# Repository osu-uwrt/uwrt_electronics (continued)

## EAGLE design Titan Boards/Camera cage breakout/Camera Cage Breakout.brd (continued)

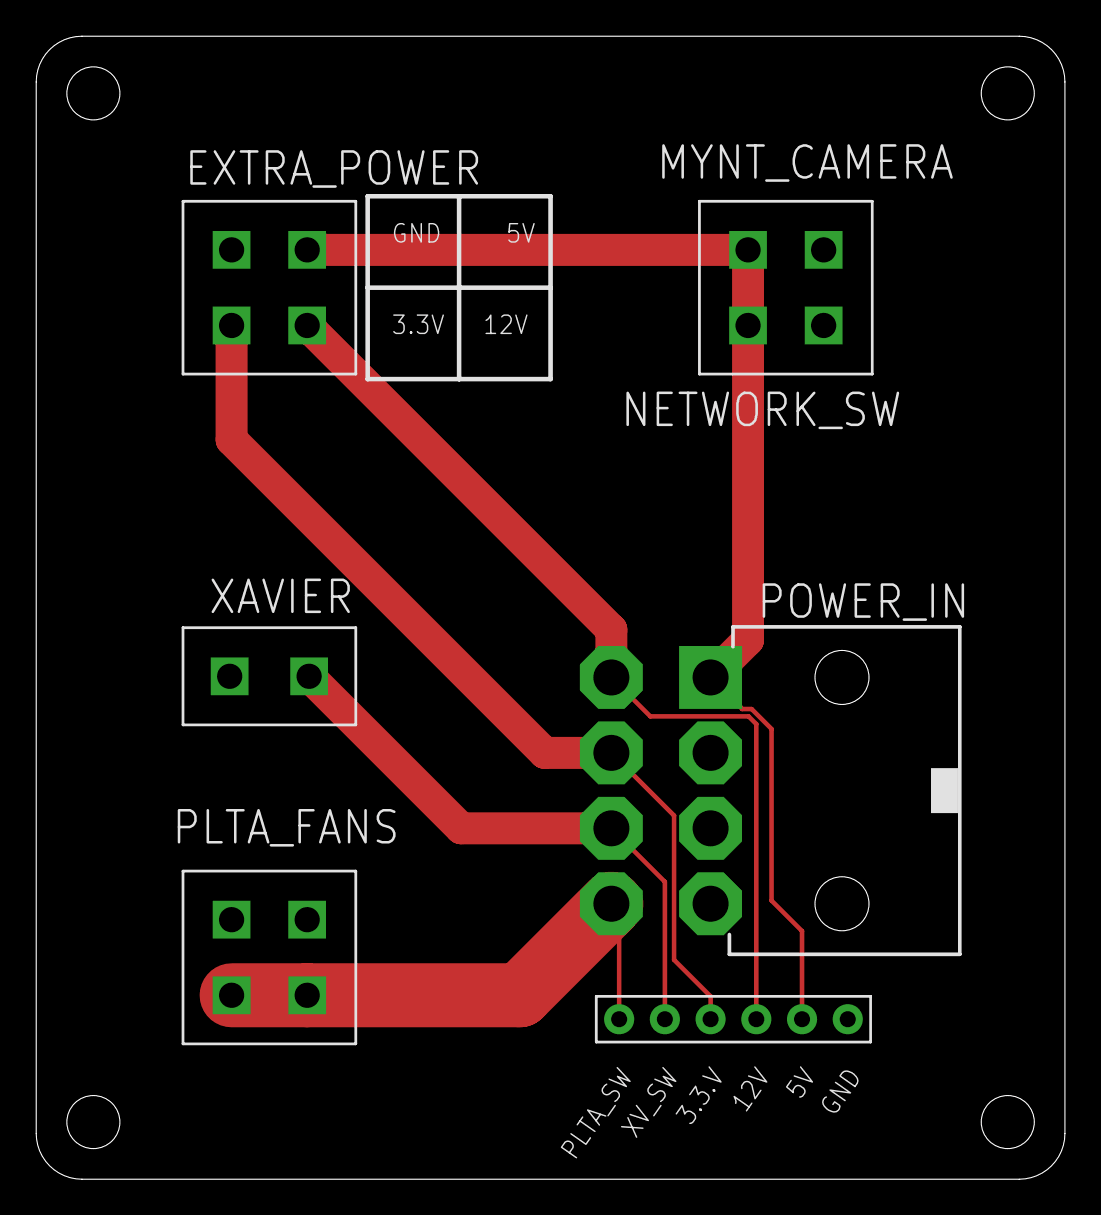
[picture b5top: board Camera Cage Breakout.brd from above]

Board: 2 copper layers, 57.1 x 63.5 mm, 6 parts (0 on the bottom side), 6 nets.

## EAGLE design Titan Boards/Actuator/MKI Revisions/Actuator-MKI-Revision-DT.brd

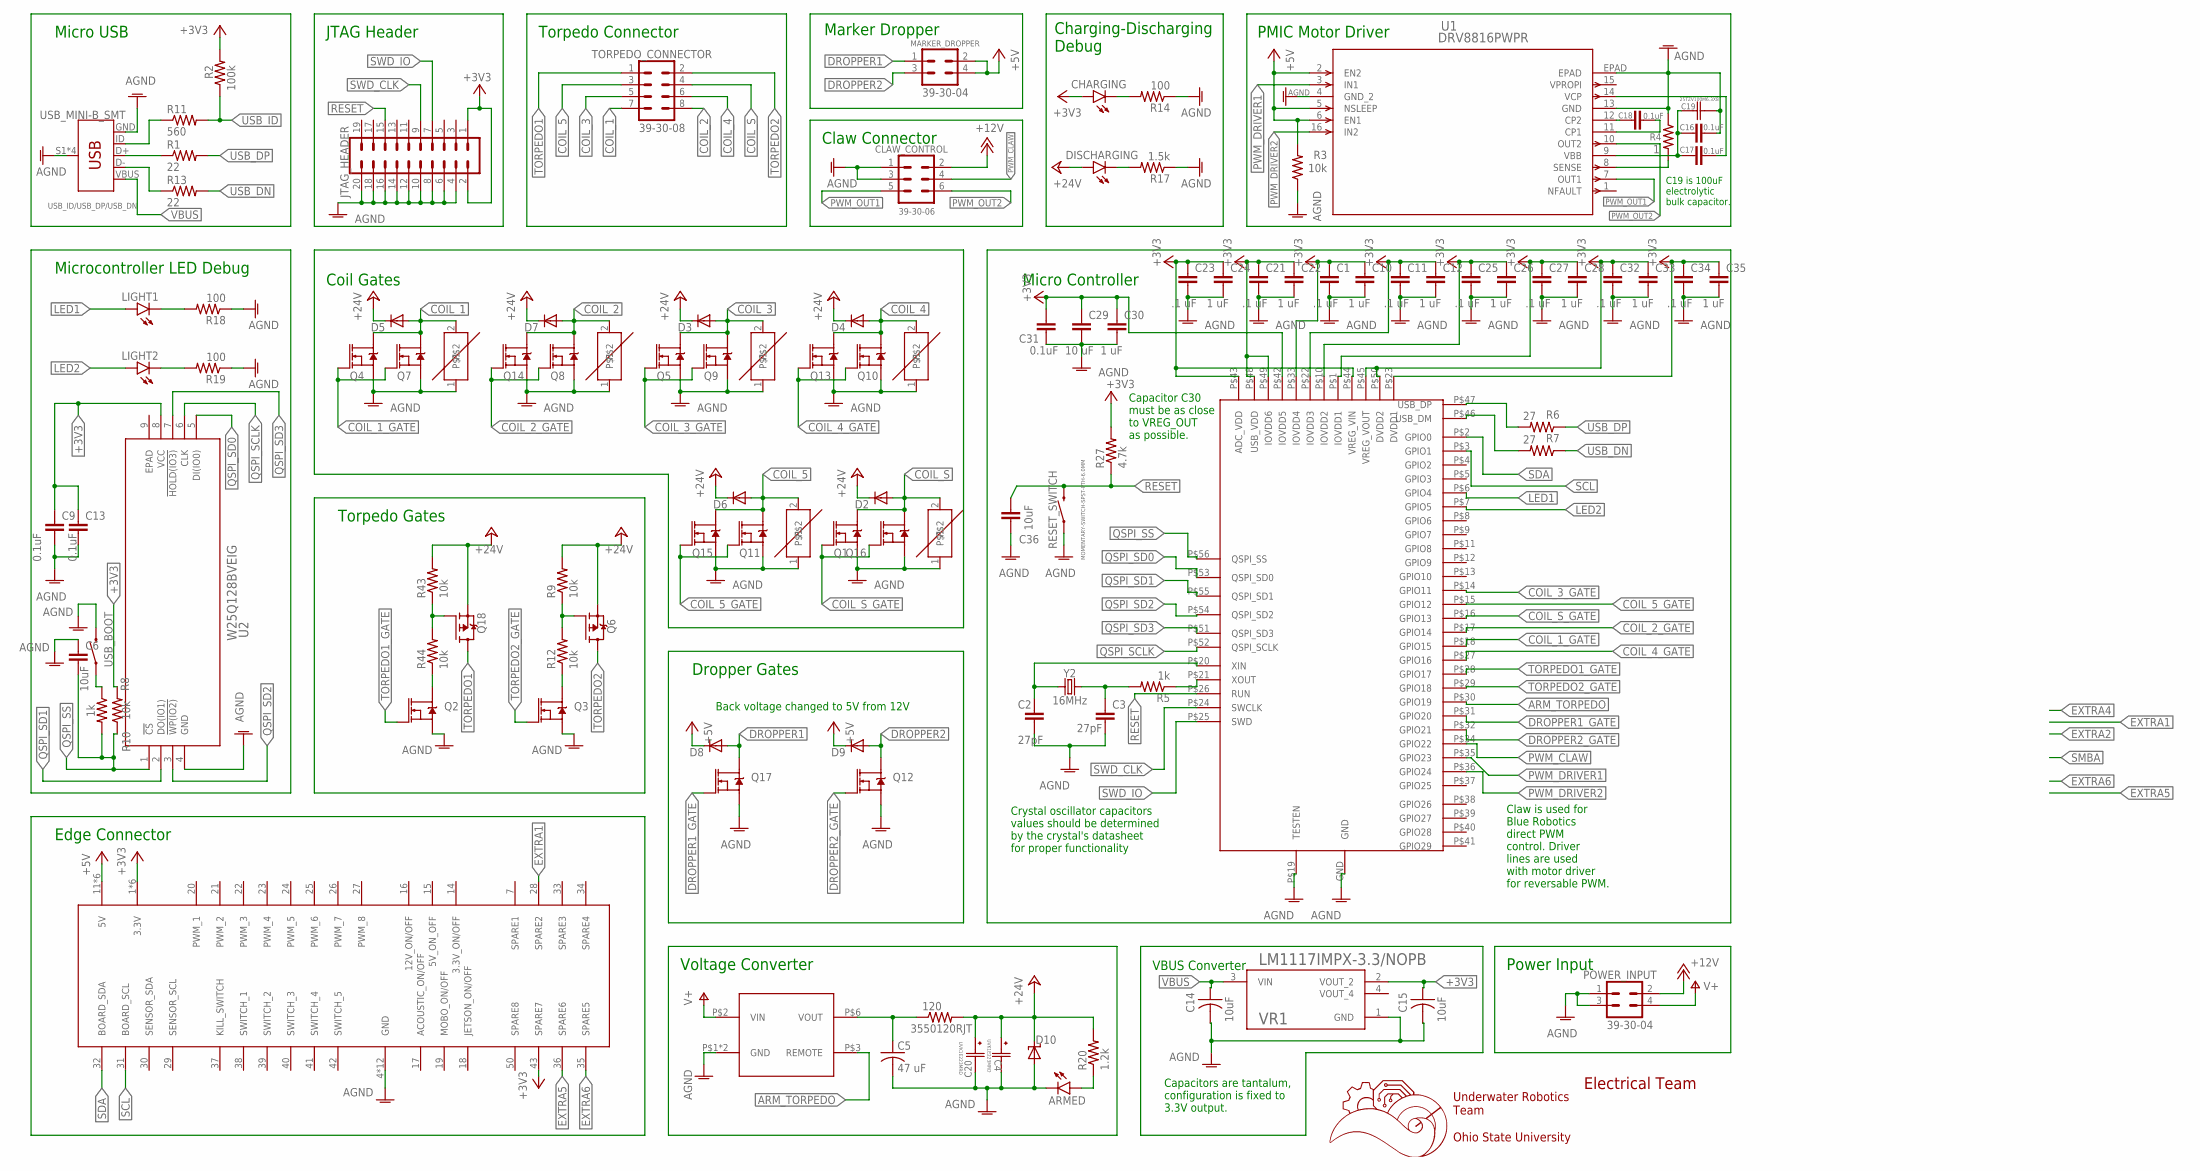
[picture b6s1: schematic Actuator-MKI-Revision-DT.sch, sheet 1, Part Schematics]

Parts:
120: 3550120RJT
ARMED: LEDCHIPLED_0603; CHIPLED_0603
C1, C11, C21, C23, C25, C27, C32, C34: .1 uF; C0603
C2, C3: 27pF; C0603
C4, C20: UVK1E223MRD; CAP_UFW_25X50_NCH
C5: 47 uF; C1206K
C6, C14, C15, C36: 10uF; C0603
C9, C13, C16, C17, C18, C31: 0.1uF; C0603
C10, C12, C22, C24, C26, C28, C30, C33, C35: 1 uF; C0603
C19: 25TZV100M6.3X8; CAP_J-V_6P3X8_RUB
C29: 10 uF; C0603
CHARGING: LEDCHIPLED_0603; CHIPLED_0603
CLAW_CONTROL: 39-30-06; 39-30-?06?
D2, D3, D4, D5, D6, D7, D8, D9: DIODE-SMB; SMB
D10: SUPPRESSOR-SMBJ; SMBJ
DISCHARGING: LEDCHIPLED_0603; CHIPLED_0603
JTAG_HEADER: CONN_10X2; 2X10
LIGHT1, LIGHT2: LEDCHIPLED_0603; CHIPLED_0603
MARKER_DROPPER: 39-30-04; 39-30-?04?
POWER_INPUT: 39-30-04; 39-30-?04?
Q1, Q2, Q3, Q4, Q5, Q7, Q8, Q9, Q10, Q11, Q12, Q13, Q14, Q15, Q16, Q17: MOSFET-NCH-AO3404A; SOT23-3
Q6, Q18: FDD4141TO252; TO252
R1, R13: 22; R0603
R2: 100k; R0603
R3, R8, R9, R12, R43, R44: 10k; R0603
R4: 1; R0805
R5, R10: 1k; R0603
R6, R7: 27; R0603
R11: 560; R0603
R14, R18, R19: 100; R0805
R17: 1.5k; R0805
R20: 1.2k; R0805
R27: 4.7k; R0603
RESET_SWITCH: MOMENTARY-SWITCH-SPST-PTH-6.0MM; TACTILE_SWITCH_PTH_6.0MM
TORPEDO_CONNECTOR: 39-30-08; 39-30-?08?
U1: DRV8816PWPR; PWP_16
U2: W25Q128BVEIG; WIN_E-8_WIN
U$1: 5530843-EDGE; 5530843-6-BOARDFINGERS
U$2, U$3, U$4, U$5, U$7, U$8: ERZ-VF2M270ERZ-VF2M270; RESM8060X320N
U$6: TMR6-2415
U$9: RP2040
USB_BOOT: MOMENTARY-SWITCH-SPST-PTH-6.0MM; TACTILE_SWITCH_PTH_6.0MM
USB_ID/USB_DP/USB_DN: USB_MINI-B_SMT; USB-MINIB
VR1: LM1117IMPX-3.3/NOPB; VREG_LM1117IMPX-3.3/NOPB
Y2: 16MHz; HC49US

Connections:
+3V3: C1.1, C9.1, C10.1, C11.1, C12.1, C13.1, C15.1, C21.1, C22.1, C23.1, C24.1, C25.1, C26.1, C27.1, C28.1, C29.1, C30.1, C31.2, C32.1, C33.1, C34.1, C35.1, CHARGING.A, JTAG_HEADER.1, JTAG_HEADER.2, R2.2, R8.2, R27.2, U2.8 (VCC), U$1.1 (3.3V), U$1.2 (3.3V), U$1.3 (3.3V), U$1.43 (SPARE7), U$1.54 (3.3V), U$1.55 (3.3V), U$1.56 (3.3V), U$9.P$1 (IOVDD1), U$9.P$10 (IOVDD2), U$9.P$22 (IOVDD3), U$9.P$23 (DVDD1), U$9.P$33 (IOVDD4), U$9.P$42 (IOVDD5), U$9.P$43 (ADC_VDD), U$9.P$44 (VREG_VIN), U$9.P$45 (VREG_VOUT), U$9.P$48 (USB_VDD), U$9.P$49 (IOVDD6), U$9.P$50 (DVDD2), VR1.2 (VOUT_2)
+5V: D8.C, D9.C, MARKER_DROPPER.2, MARKER_DROPPER.4, R3.2, U1.2 (EN2), U1.5 (NSLEEP), U1.6 (EN1), U$1.11 (5V), U$1.12 (5V), U$1.13 (5V), U$1.44 (5V), U$1.45 (5V), U$1.46 (5V)
+12V: CLAW_CONTROL.2, POWER_INPUT.2
+24V: 120.P$2 (2), C4.1, C20.1, D2.C, D3.C, D4.C, D5.C, D6.C, D7.C, D10.C, DISCHARGING.A, Q6.2 (S), Q18.2 (S), R9.2, R20.2, R43.2
AGND: ARMED.C, C1.2, C2.2, C3.2, C4.2, C5.2, C6.1, C9.2, C10.2, C11.2, C12.2, C13.2, C14.2, C15.2, C16.2, C19.2, C20.2, C21.2, C22.2, C23.2, C24.2, C25.2, C26.2, C27.2, C28.2, C29.2, C30.2, C31.1, C32.2, C33.2, C34.2, C35.2, C36.1, CLAW_CONTROL.1, CLAW_CONTROL.3, D10.A, JTAG_HEADER.4, JTAG_HEADER.6, JTAG_HEADER.8, JTAG_HEADER.10, JTAG_HEADER.12, JTAG_HEADER.14, JTAG_HEADER.16, JTAG_HEADER.18, JTAG_HEADER.20, POWER_INPUT.1, POWER_INPUT.3, Q1.2 (S), Q2.2 (S), Q3.2 (S), Q4.2 (S), Q5.2 (S), Q7.2 (S), Q8.2 (S), Q9.2 (S), Q10.2 (S), Q11.2 (S), Q12.2 (S), Q13.2 (S), Q14.2 (S), Q15.2 (S), Q16.2 (S), Q17.2 (S), R3.1, R4.1, R14.1, R17.1, R18.1, R19.1, RESET_SWITCH.1, U1.4 (GND_2), U1.13 (GND), U1.EPAD, U2.4 (GND), U$1.4 (GND), U$1.5 (GND), U$1.6 (GND), U$1.8 (GND), U$1.9 (GND), U$1.10 (GND), U$1.47 (GND), U$1.48 (GND), U$1.49 (GND), U$1.51 (GND), U$1.52 (GND), U$1.53 (GND), U$2.1, U$3.1, U$4.1, U$5.1, U$6.P$1 (GND), U$6.P$7 (GND), U$7.1, U$8.1, U$9.GND, U$9.P$19 (TESTEN), USB_BOOT.3 (2), USB_ID/USB_DP/USB_DN.GND, USB_ID/USB_DP/USB_DN.S1 (SHIELD), USB_ID/USB_DP/USB_DN.S2 (SHIELD), USB_ID/USB_DP/USB_DN.S3 (SHIELD), USB_ID/USB_DP/USB_DN.S4 (SHIELD), VR1.1 (GND)
ARM_TORPEDO: U$6.P$3 (REMOTE), U$9.P$30 (GPIO19)
COIL_1: D5.A, Q4.3 (D), Q7.3 (D), TORPEDO_CONNECTOR.7, U$8.2
COIL_1_GATE: Q4.1 (G), Q7.1 (G), U$9.P$18 (GPIO15)
COIL_2: D7.A, Q8.3 (D), Q14.3 (D), TORPEDO_CONNECTOR.8, U$7.2
COIL_2_GATE: Q8.1 (G), Q14.1 (G), U$9.P$17 (GPIO14)
COIL_3: D3.A, Q5.3 (D), Q9.3 (D), TORPEDO_CONNECTOR.5, U$5.2
COIL_3_GATE: Q5.1 (G), Q9.1 (G), U$9.P$14 (GPIO11)
COIL_4: D4.A, Q10.3 (D), Q13.3 (D), TORPEDO_CONNECTOR.6, U$4.2
COIL_4_GATE: Q10.1 (G), Q13.1 (G), U$9.P$27 (GPIO16)
COIL_5: D6.A, Q11.3 (D), Q15.3 (D), TORPEDO_CONNECTOR.3, U$3.2
COIL_5_GATE: Q11.1 (G), Q15.1 (G), U$9.P$15 (GPIO12)
COIL_S: D2.A, Q1.3 (D), Q16.3 (D), TORPEDO_CONNECTOR.4, U$2.2
COIL_S_GATE: Q1.1 (G), Q16.1 (G), U$9.P$16 (GPIO13)
DROPPER1: D8.A, MARKER_DROPPER.1, Q17.3 (D)
DROPPER1_GATE: Q17.1 (G), U$9.P$31 (GPIO20)
DROPPER2: D9.A, MARKER_DROPPER.3, Q12.3 (D)
DROPPER2_GATE: Q12.1 (G), U$9.P$32 (GPIO21)
EXTRA1: U$1.28 (SPARE2)
EXTRA5: U$1.36 (SPARE6)
EXTRA6: U$1.35 (SPARE5)
LED1: LIGHT1.A, U$9.P$6 (GPIO4)
LED2: LIGHT2.A, U$9.P$7 (GPIO5)
unnamed: C3.1, R5.2, Y2.2
unnamed: R5.1, U$9.P$21 (XOUT)
unnamed: CHARGING.C, R14.2
unnamed: R11.1, USB_ID/USB_DP/USB_DN.ID
unnamed: R1.1, USB_ID/USB_DP/USB_DN.D+
unnamed: R13.1, USB_ID/USB_DP/USB_DN.D-
unnamed: ARMED.A, R20.1
unnamed: C2.1, U$9.P$20 (XIN), Y2.1
unnamed: R6.2, U$9.P$47 (USB_DP)
unnamed: DISCHARGING.C, R17.2
unnamed: LIGHT1.C, R18.2
unnamed: LIGHT2.C, R19.2
unnamed: R10.1, USB_BOOT.1
unnamed: 120.P$1 (1), C5.1, U$6.P$6 (VOUT)
unnamed: R7.2, U$9.P$46 (USB_DM)
unnamed: Q18.1 (G), R43.1, R44.2
unnamed: Q2.3 (D), R44.1
unnamed: Q6.1 (G), R9.1, R12.2
unnamed: Q3.3 (D), R12.1
unnamed: R4.2, U1.8 (SENSE)
unnamed: C17.2, U1.14 (VCP)
unnamed: C16.1, C17.1, C19.1, U1.9 (VBB)
unnamed: C18.2, U1.11 (CP1)
unnamed: C18.1, U1.12 (CP2)
PWM_CLAW: CLAW_CONTROL.4, U$9.P$34 (GPIO22)
PWM_DRIVER1: U1.3 (IN1), U$9.P$35 (GPIO23)
PWM_DRIVER2: U1.16 (IN2), U$9.P$36 (GPIO24)
PWM_OUT1: CLAW_CONTROL.5, U1.7 (OUT1)
PWM_OUT2: CLAW_CONTROL.6, U1.10 (OUT2)
QSPI_SCLK: U2.6 (CLK), U$9.P$52 (QSPI_SCLK)
QSPI_SD0: U2.5 (DI(IO0)), U$9.P$53 (QSPI_SD0)
QSPI_SD1: U2.2 (DO(IO1)), U$9.P$55 (QSPI_SD1)
QSPI_SD2: U2.3 (!WP(IO2)), U$9.P$54 (QSPI_SD2)
QSPI_SD3: U2.7 (!HOLD(IO3)), U$9.P$51 (QSPI_SD3)
QSPI_SS: C6.2, R8.1, R10.2, U2.1 (!CS), U$9.P$56 (QSPI_SS)
RESET: C36.2, JTAG_HEADER.15, R27.1, RESET_SWITCH.3 (2), U$9.P$26 (RUN)
SCL: U$1.31 (BOARD_SCL), U$9.P$3 (GPIO1)
SDA: U$1.32 (BOARD_SDA), U$9.P$2 (GPIO0)
SWD_CLK: JTAG_HEADER.9, U$9.P$24 (SWCLK)
SWD_IO: JTAG_HEADER.7, U$9.P$25 (SWD)
TORPEDO1: Q18.3 (D), TORPEDO_CONNECTOR.1
TORPEDO1_GATE: Q2.1 (G), U$9.P$28 (GPIO17)
TORPEDO2: Q6.3 (D), TORPEDO_CONNECTOR.2
TORPEDO2_GATE: Q3.1 (G), U$9.P$29 (GPIO18)
USB_DN: R7.1, R13.2
USB_DP: R1.2, R6.1
USB_ID: R2.1, R11.2
V+: POWER_INPUT.4, U$6.P$2 (VIN)
VBUS: C14.1, USB_ID/USB_DP/USB_DN.VBUS, VR1.3 (VIN)

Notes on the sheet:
Underwater Robotics Team Ohio State University
Electrical Team
Micro USB
JTAG Header
Torpedo Connector
Claw Connector
Charging-Discharging Debug
Microcontroller LED Debug
Edge Connector
Voltage Converter
Crystal oscillator capacitors values should be determined by the crystal's datasheet for proper functionality
Dropper Gates
Coil Gates
Torpedo Gates
Marker Dropper
Power Input
Micro Controller
Back voltage changed to 5V from 12V
Capacitors are tantalum, configuration is fixed to 3.3V output.
VBUS Converter
PMIC Motor Driver
Claw is used for Blue Robotics direct PWM control. Driver lines are used with motor driver for reversable PWM.
C19 is 100uF electrolytic bulk capacitor.
Capacitor C30 must be as close to VREG_OUT as possible.

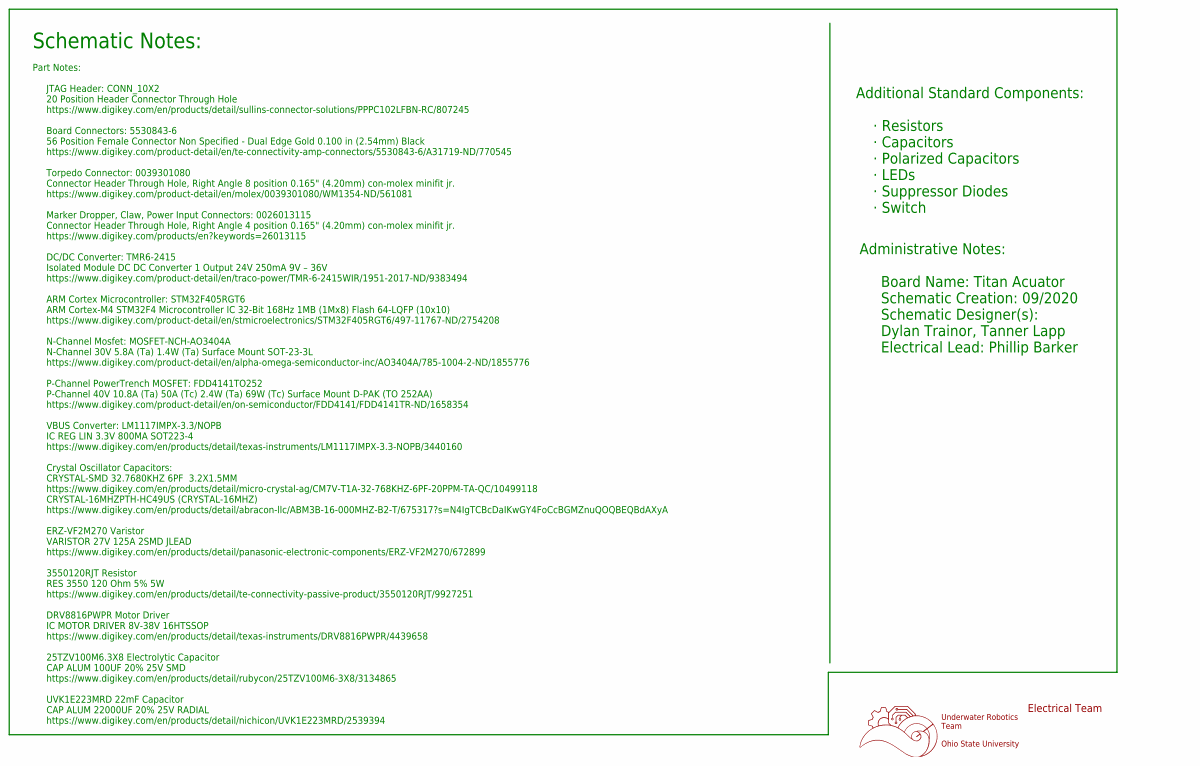
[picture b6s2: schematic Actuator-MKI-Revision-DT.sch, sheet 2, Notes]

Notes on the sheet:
Underwater Robotics Team Ohio State University
Electrical Team
Schematic Notes:
Part Notes: JTAG Header: CONN_10X2 20 Position Header Connector Through Hole https://www.digikey.com/en/products/detail/sullins-connector-solutions/PPPC102LFBN-RC/807245 Board Connectors: 5530843-6 56 Position Female Connector Non Specified - Dual Edge Gold 0.100 in (2.54mm) Black https://www.digik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
Administrative Notes: Board Name: Titan Acuator Schematic Creation: 09/2020 Schematic Designer(s): Dylan Trainor, Tanner Lapp Electrical Lead: Phillip Barker
Additional Standard Components: · Resistors · Capacitors · Polarized Capacitors · LEDs · Suppressor Diodes · Switch

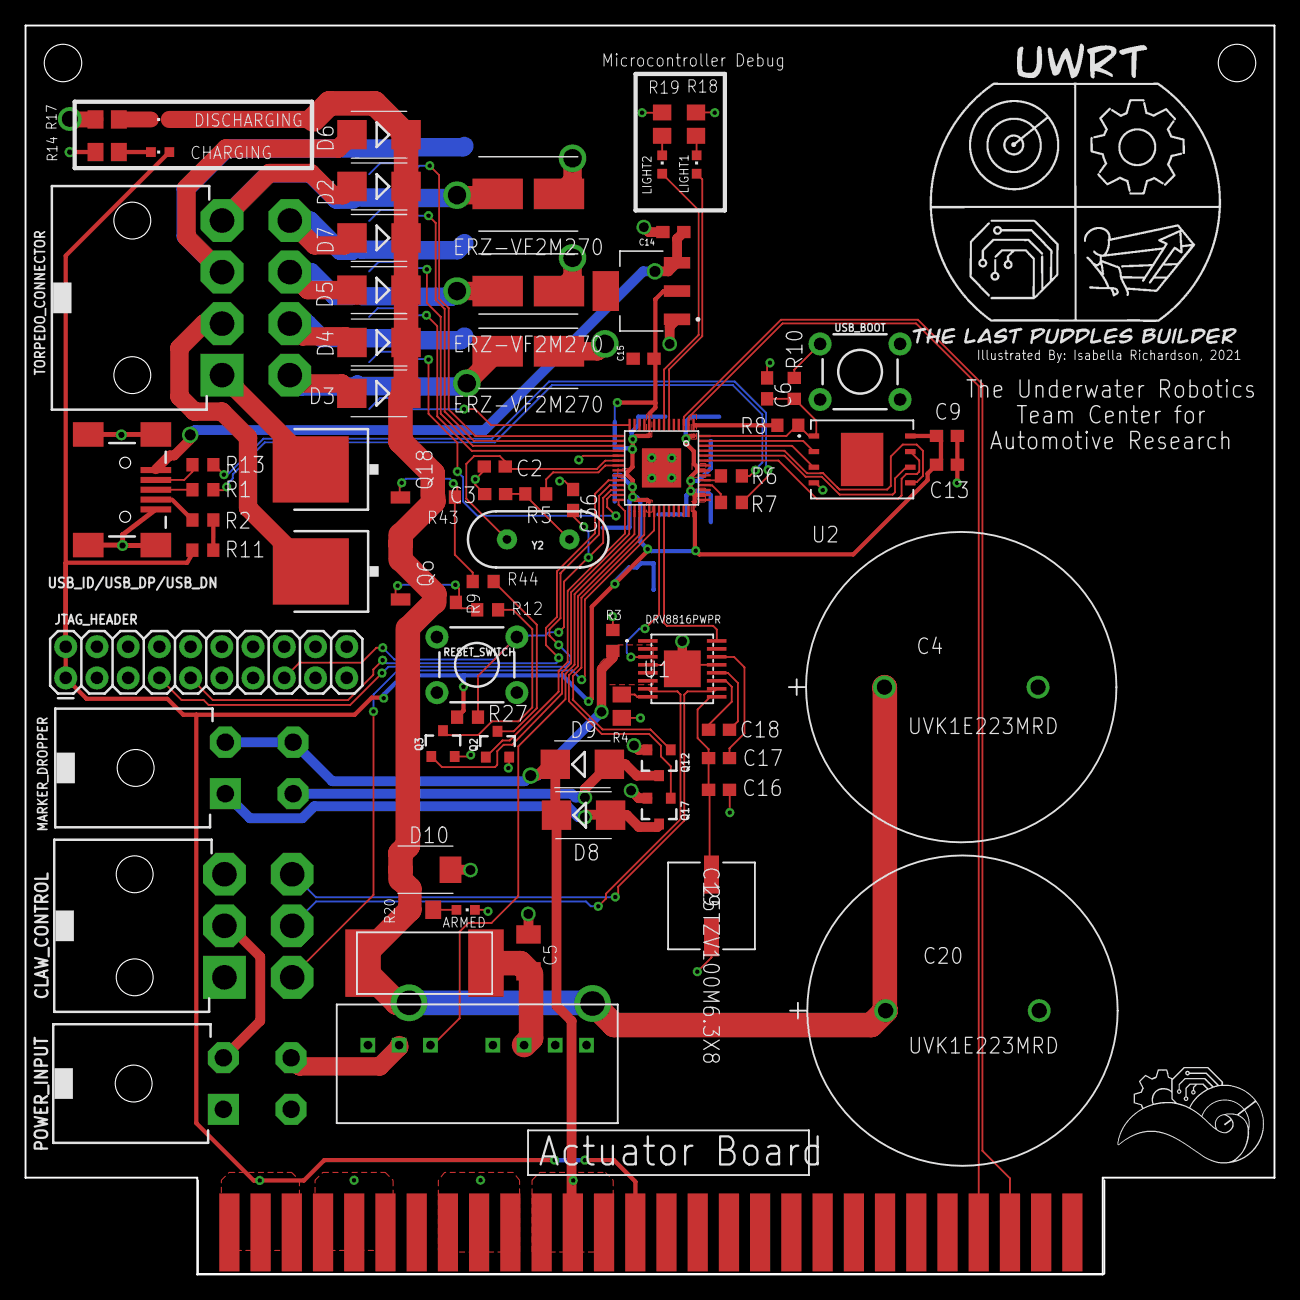
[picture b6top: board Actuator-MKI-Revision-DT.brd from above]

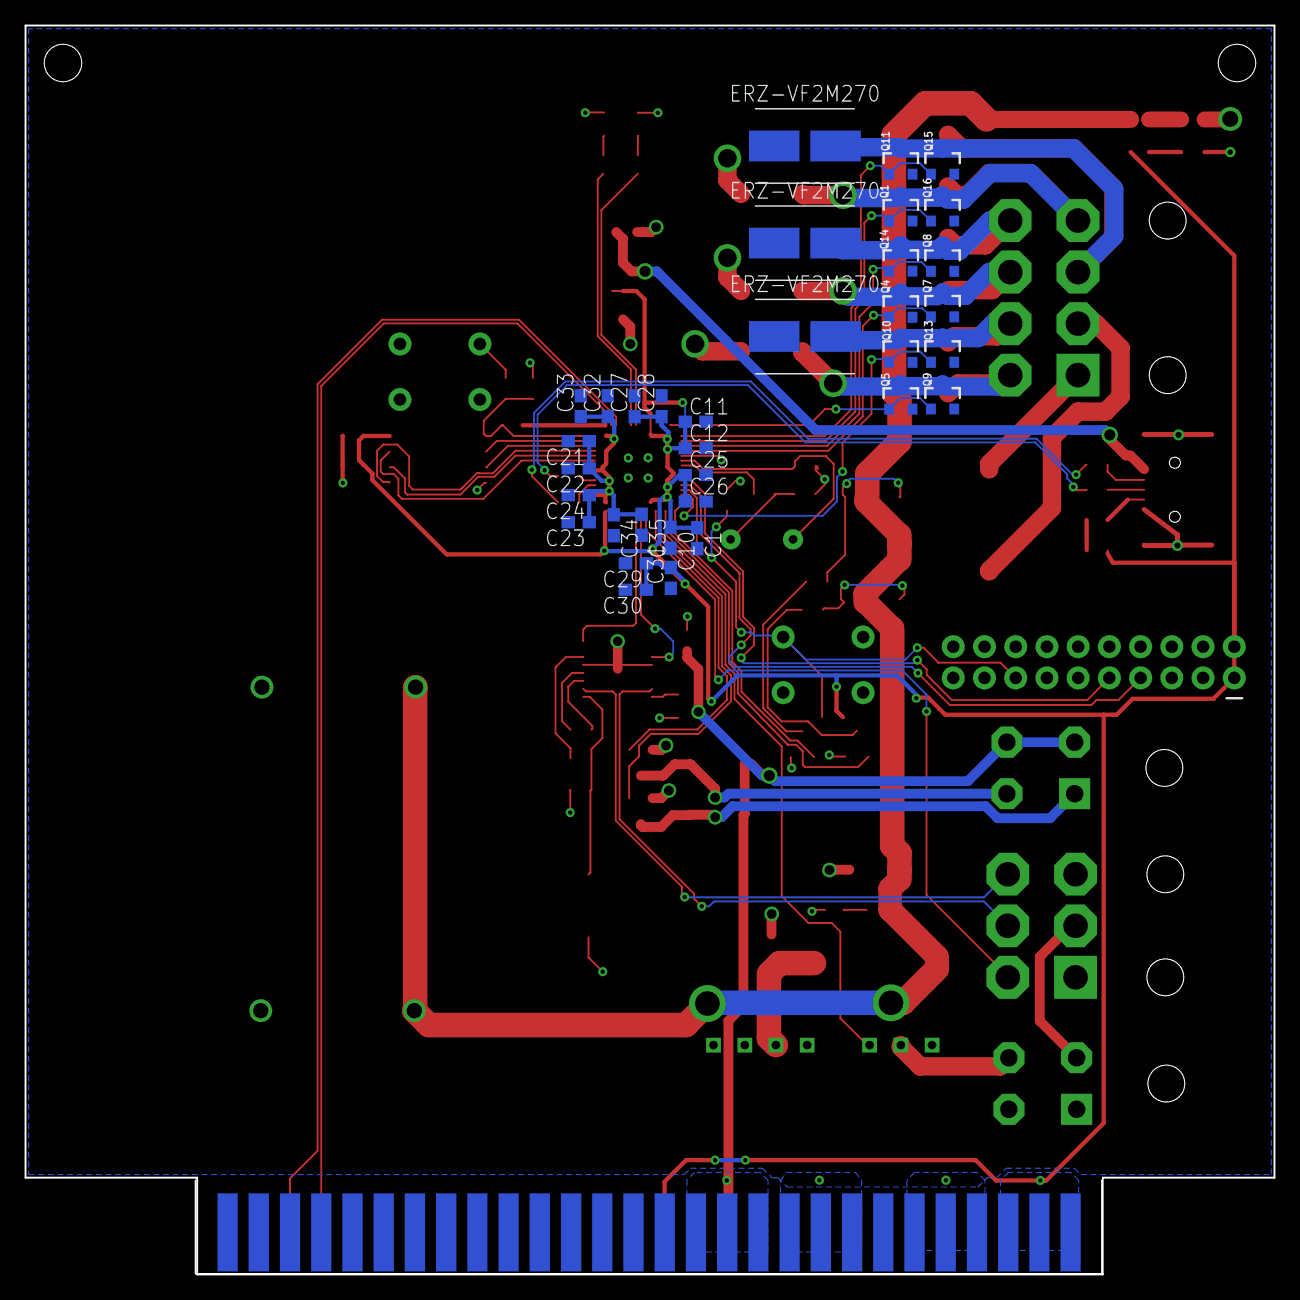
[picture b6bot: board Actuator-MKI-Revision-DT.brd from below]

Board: 2 copper layers, 101.6 x 101.6 mm, 109 parts (34 on the bottom side), 73 nets.

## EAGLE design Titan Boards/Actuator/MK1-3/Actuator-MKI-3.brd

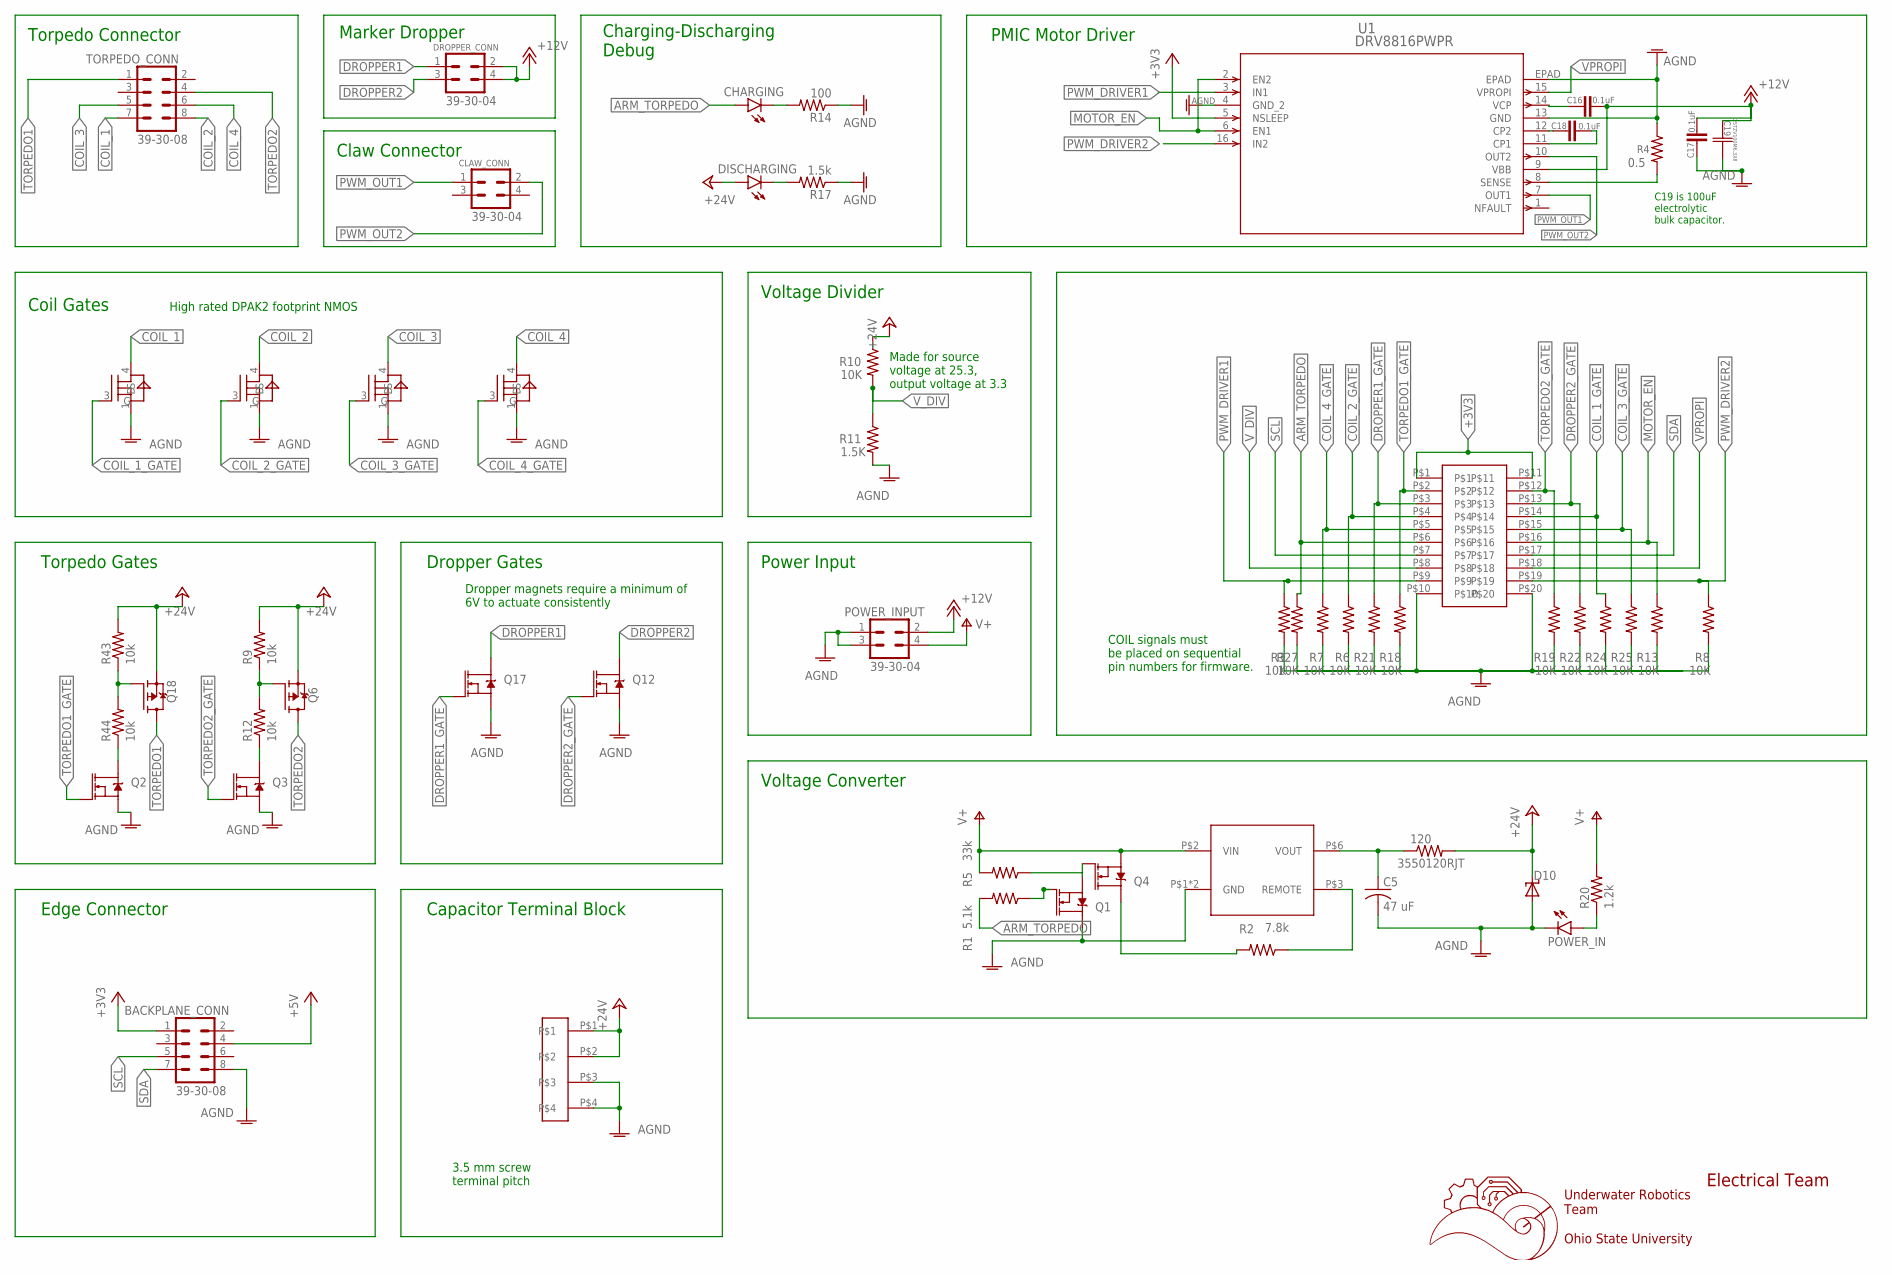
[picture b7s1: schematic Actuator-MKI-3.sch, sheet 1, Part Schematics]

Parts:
120: 3550120RJT
BACKPLANE_CONN: 39-30-08; 39-30-?08?
C5: 47 uF; C1206K
C16, C17, C18: 0.1uF; C0603
C19: 25TZV100M6.3X8; CAP_J-V_6P3X8_RUB
CHARGING: LEDCHIPLED_0603; CHIPLED_0603
CLAW_CONN: 39-30-04; 39-30-?04?
D10: SUPPRESSOR-SMBJ; SMBJ
DISCHARGING: LEDCHIPLED_0603; CHIPLED_0603
DROPPER_CONN: 39-30-04; 39-30-?04?
POWER_IN: LEDCHIPLED_0603; CHIPLED_0603
POWER_INPUT: 39-30-04; 39-30-?04?
Q1, Q2, Q3, Q4, Q12, Q17: MOSFET-NCH-AO3404A; SOT23-3
Q6, Q18: FDD4141TO252; TO252
R1: 5.1k; R0603
R2: 7.8k; R0603
R3, R6, R7, R8, R10, R13, R18, R19, R21, R22, R24, R25, R27: 10K; R0603
R4: 0.5; R0805
R5: 33k; R0603
R9, R12, R43, R44: 10k; R0603
R11: 1.5K; R0603
R14: 100; R0805
R17: 1.5k; R0805
R20: 1.2k; R0805
TORPEDO_CONN: 39-30-08; 39-30-?08?
U1: DRV8816PWPR; PWP_16
U2, U3, U4, U5: MBRB2060CTT4G; D2PAK3-4_9P65X10P29_ONS
U$1: 31059104
U$2: JTAG-SMD
U$6: TMR6-2415

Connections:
+3V3: BACKPLANE_CONN.1, U1.5 (NSLEEP), U$2.P$1, U$2.P$11
+5V: BACKPLANE_CONN.4
+12V: C16.2, C17.2, C19.1, DROPPER_CONN.2, DROPPER_CONN.4, POWER_INPUT.2, U1.9 (VBB)
+24V: 120.P$2 (2), D10.C, DISCHARGING.A, Q6.2 (S), Q18.2 (S), R9.2, R10.1, R43.2, U$1.P$1, U$1.P$2
AGND: BACKPLANE_CONN.8, C5.2, C17.1, C19.2, D10.A, POWER_IN.C, POWER_INPUT.1, POWER_INPUT.3, Q1.3 (D), Q2.2 (S), Q3.2 (S), Q12.2 (S), Q17.2 (S), R3.2, R4.1, R6.2, R7.2, R8.2, R11.2, R13.2, R14.1, R17.1, R18.2, R19.2, R21.2, R22.2, R24.2, R25.2, R27.2, U1.4 (GND_2), U1.13 (GND), U1.EPAD, U2.1 (S), U3.1 (S), U4.1 (S), U5.1 (S), U$1.P$3, U$1.P$4, U$2.P$10, U$2.P$20, U$6.P$1 (GND), U$6.P$7 (GND)
ARM_TORPEDO: CHARGING.A, R1.2, R27.1, U$2.P$6
COIL_1: TORPEDO_CONN.7, U2.4 (D)
COIL_1_GATE: R24.1, U2.3 (G), U$2.P$14
COIL_2: TORPEDO_CONN.8, U3.4 (D)
COIL_2_GATE: R6.1, U3.3 (G), U$2.P$4
COIL_3: TORPEDO_CONN.5, U4.4 (D)
COIL_3_GATE: R25.1, U4.3 (G), U$2.P$15
COIL_4: TORPEDO_CONN.6, U5.4 (D)
COIL_4_GATE: R7.1, U5.3 (G), U$2.P$5
DROPPER1: DROPPER_CONN.1, Q17.3 (D)
DROPPER1_GATE: Q17.1 (G), R21.1, U$2.P$3
DROPPER2: DROPPER_CONN.3, Q12.3 (D)
DROPPER2_GATE: Q12.1 (G), R22.1, U$2.P$13
MOTOR_EN: R13.1, U1.2 (EN2), U1.6 (EN1), U$2.P$16
unnamed: C16.1, U1.14 (VCP)
unnamed: R2.1, U$6.P$3 (REMOTE)
unnamed: CHARGING.C, R14.2
unnamed: Q1.1 (G), R1.1
unnamed: Q1.2 (S), Q4.1 (G), R5.1
unnamed: Q4.3 (D), R2.2
unnamed: POWER_IN.A, R20.1
unnamed: DISCHARGING.C, R17.2
unnamed: 120.P$1 (1), C5.1, U$6.P$6 (VOUT)
unnamed: Q18.1 (G), R43.1, R44.2
unnamed: Q2.3 (D), R44.1
unnamed: Q6.1 (G), R9.1, R12.2
unnamed: Q3.3 (D), R12.1
unnamed: R4.2, U1.8 (SENSE)
unnamed: C18.2, U1.11 (CP1)
unnamed: C18.1, U1.12 (CP2)
PWM_DRIVER1: R3.1, U1.3 (IN1), U$2.P$9
PWM_DRIVER2: R8.1, U1.16 (IN2), U$2.P$19
PWM_OUT1: CLAW_CONN.1, U1.7 (OUT1)
PWM_OUT2: CLAW_CONN.2, U1.10 (OUT2)
SCL: BACKPLANE_CONN.5, U$2.P$7
SDA: BACKPLANE_CONN.7, U$2.P$17
TORPEDO1: Q18.3 (D), TORPEDO_CONN.1
TORPEDO1_GATE: Q2.1 (G), R18.1, U$2.P$2
TORPEDO2: Q6.3 (D), TORPEDO_CONN.4
TORPEDO2_GATE: Q3.1 (G), R19.1, U$2.P$12
V+: POWER_INPUT.4, Q4.2 (S), R5.2, R20.2, U$6.P$2 (VIN)
VPROPI: U1.15 (VPROPI), U$2.P$18
V_DIV: R10.2, R11.1, U$2.P$8

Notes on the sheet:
Underwater Robotics Team Ohio State University
Electrical Team
Torpedo Connector
Claw Connector
Charging-Discharging Debug
Edge Connector
Voltage Converter
Dropper Gates
Coil Gates
Torpedo Gates
Marker Dropper
Power Input
Dropper magnets require a minimum of 6V to actuate consistently
PMIC Motor Driver
C19 is 100uF electrolytic bulk capacitor.
Made for source voltage at 25.3, output voltage at 3.3
Voltage Divider
High rated DPAK2 footprint NMOS
3.5 mm screw terminal pitch
COIL signals must be placed on sequential pin numbers for firmware.
Capacitor Terminal Block

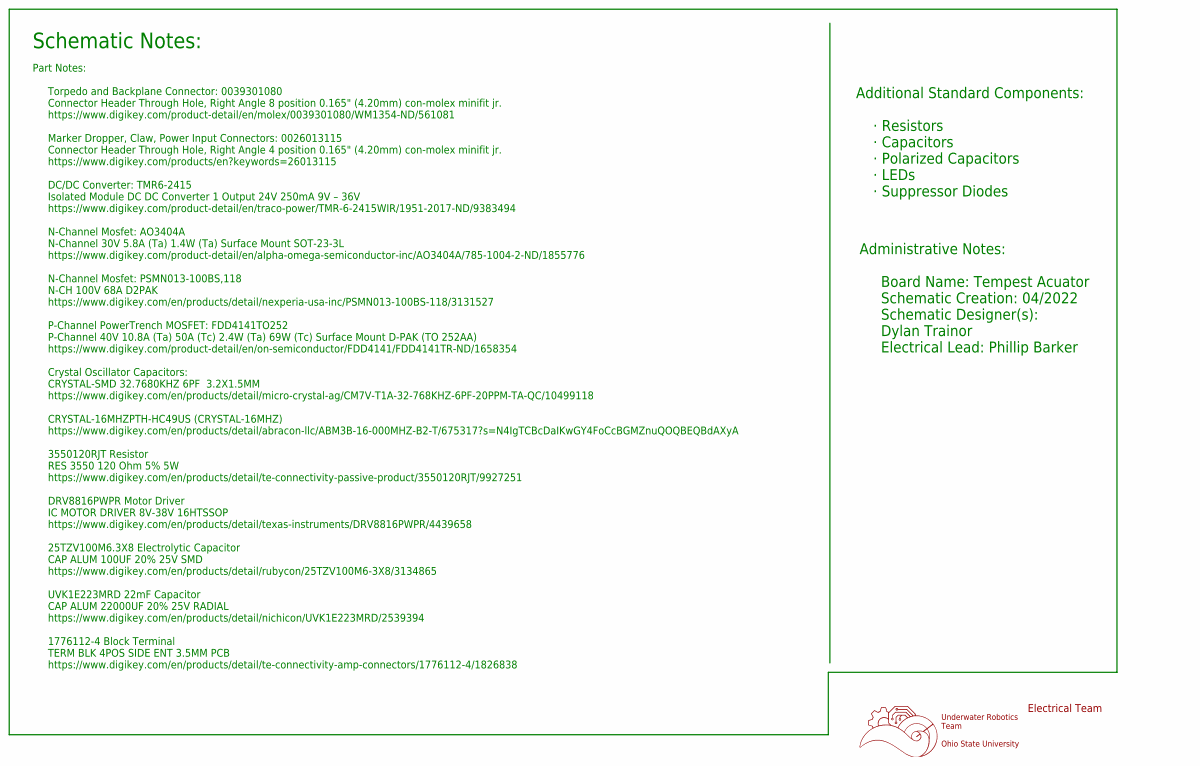
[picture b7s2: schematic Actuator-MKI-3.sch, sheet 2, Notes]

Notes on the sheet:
Underwater Robotics Team Ohio State University
Electrical Team
Schematic Notes:
Part Notes: Torpedo and Backplane Connector: 0039301080 Connector Header Through Hole, Right Angle 8 position 0.165" (4.20mm) con-molex minifit jr. https://www.digikey.com/product-detail/en/molex/0039301080/WM1354-ND/561081 Marker Dropper, Claw, Power Input Connectors: 0026013115 Connector Header T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
Administrative Notes: Board Name: Tempest Acuator Schematic Creation: 04/2022 Schematic Designer(s): Dylan Trainor Electrical Lead: Phillip Barker
Additional Standard Components: · Resistors · Capacitors · Polarized Capacitors · LEDs · Suppressor Diodes

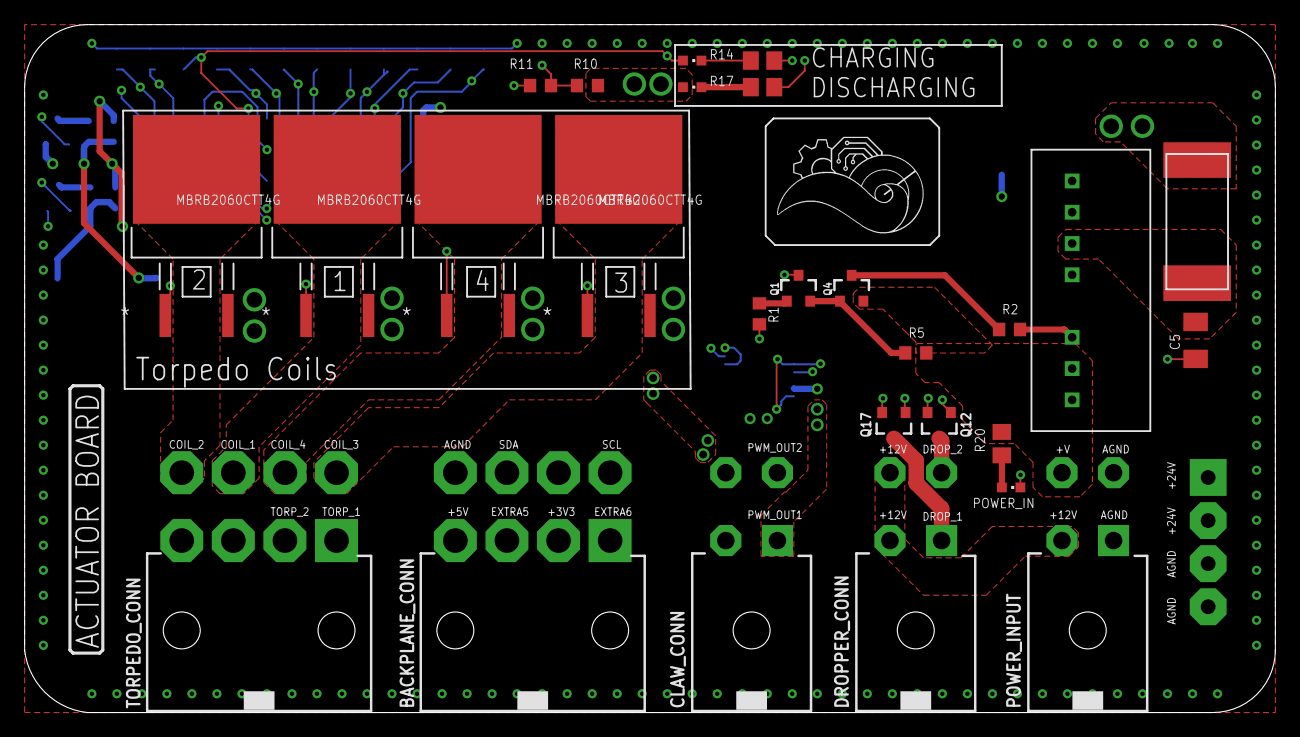
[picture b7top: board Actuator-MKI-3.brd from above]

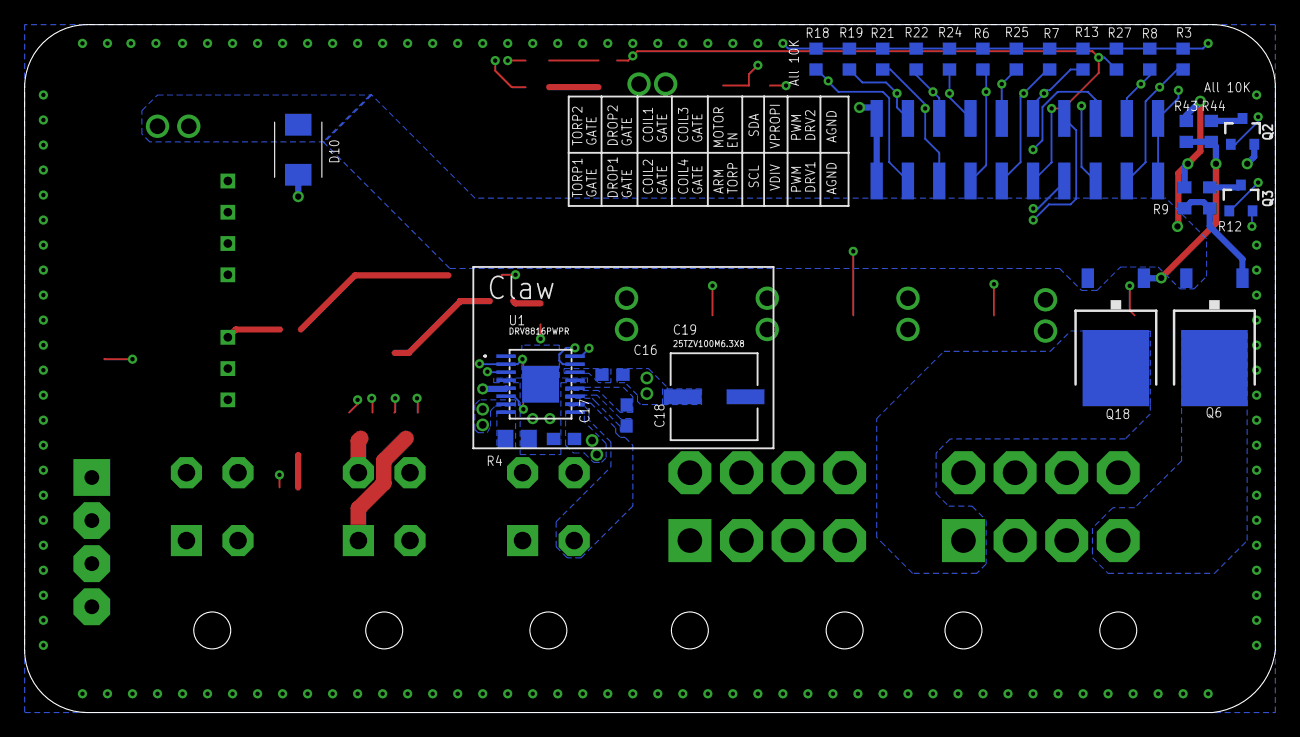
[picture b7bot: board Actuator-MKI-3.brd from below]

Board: 4 copper layers, 101.6 x 55.9 mm, 56 parts (28 on the bottom side), 47 nets.
